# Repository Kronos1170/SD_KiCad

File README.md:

# IBM Card Reader

KiCad 10 project for the IBM card reader prototype board (ESP32-S3).

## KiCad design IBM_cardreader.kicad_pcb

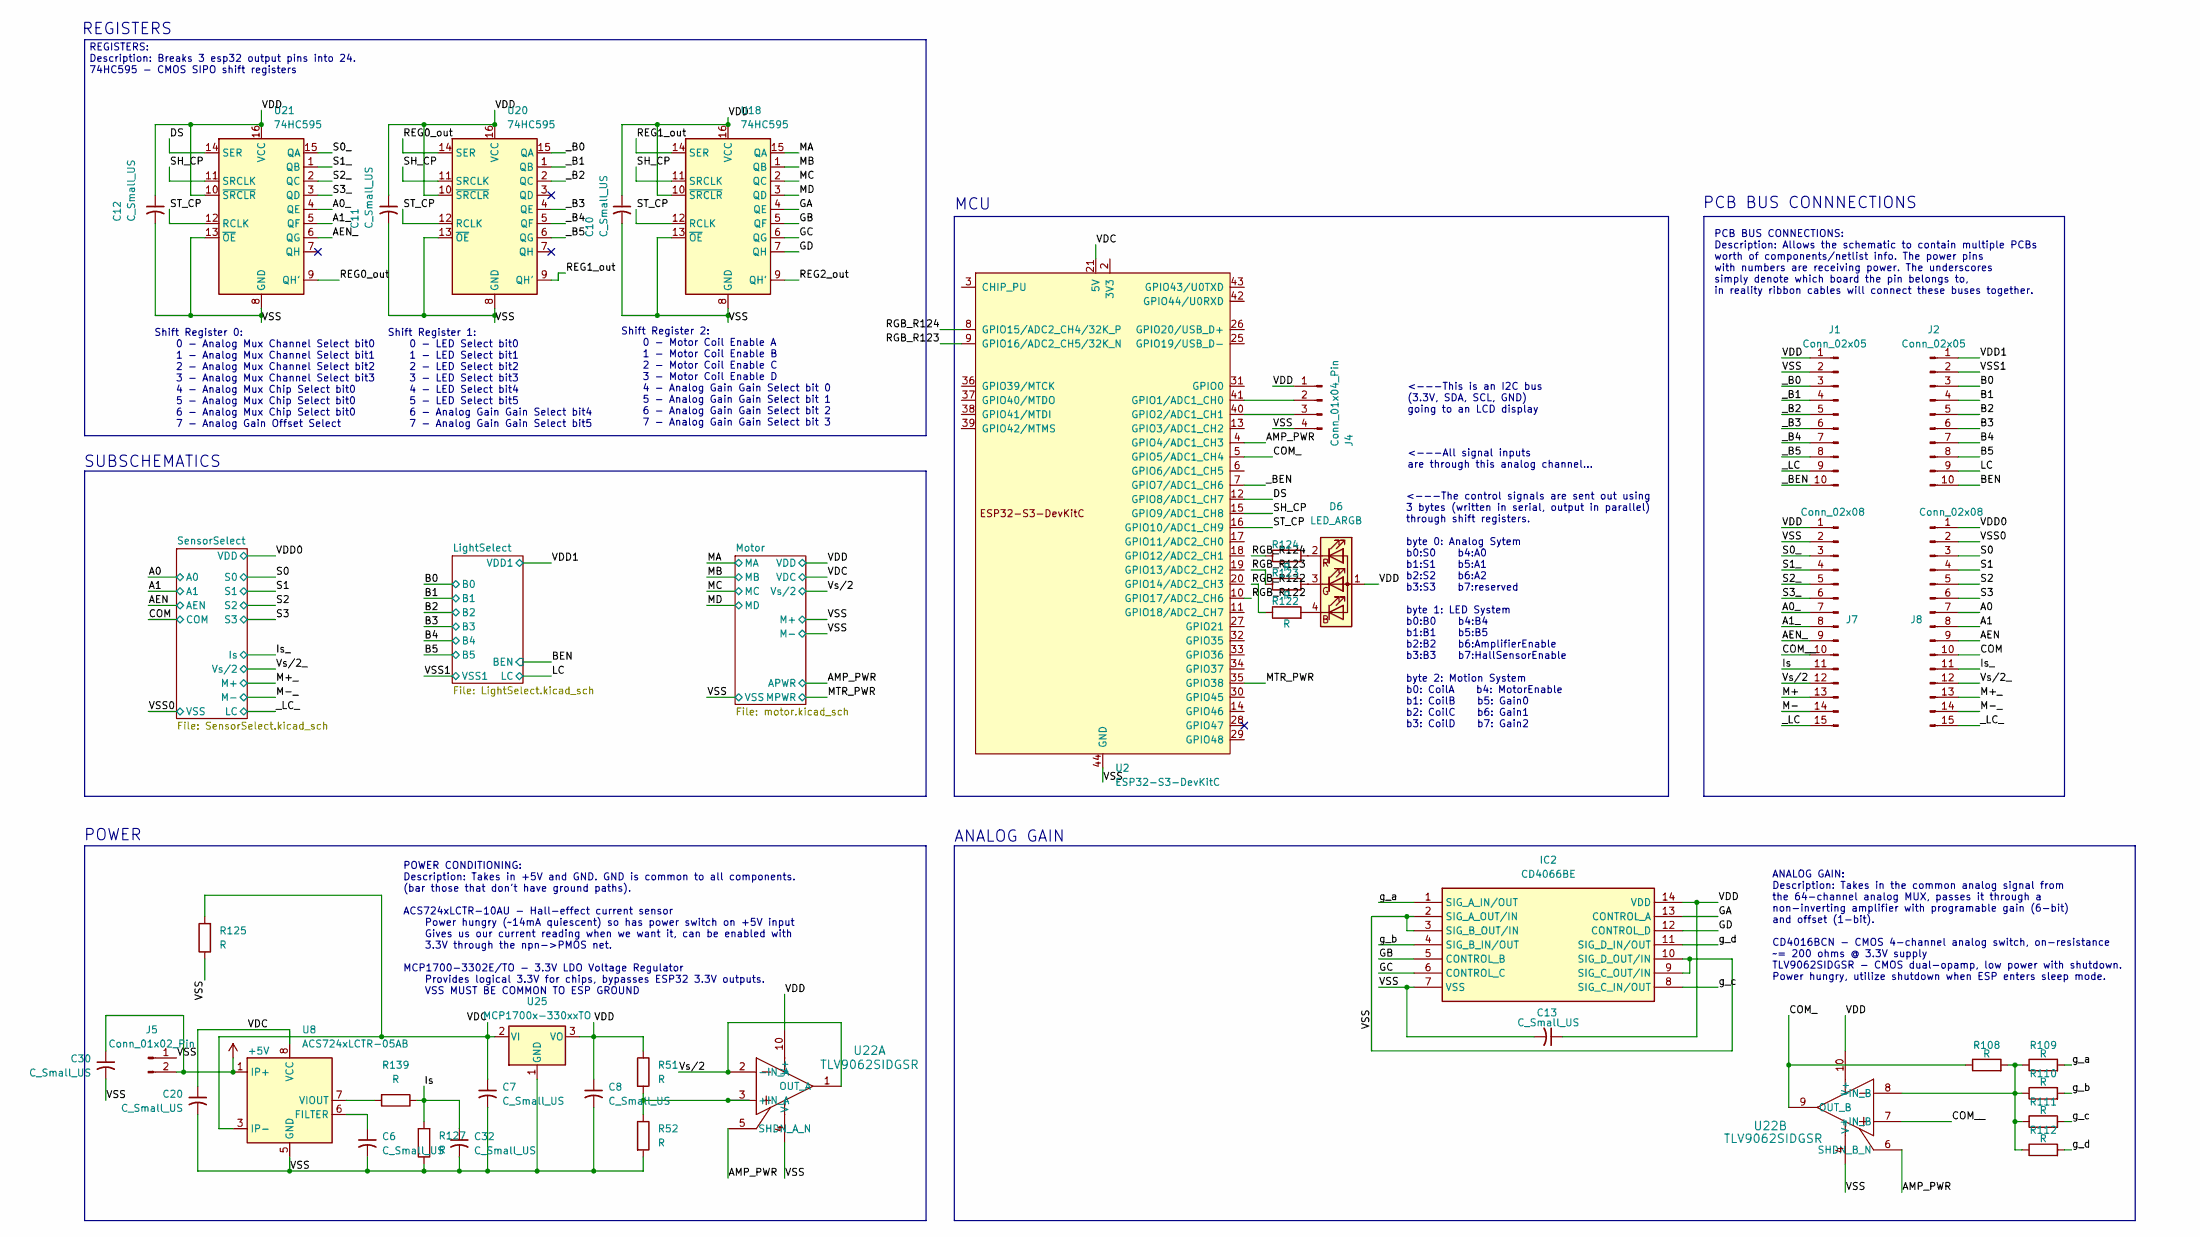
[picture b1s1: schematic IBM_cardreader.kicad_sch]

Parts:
C6, C7, C8, C10, C11, C12, C13, C20, C30, C32: C_Small_US; C_Disc_D3.0mm_W1.6mm_P2.50mm
D6: LED_ARGB; LED_RGB_1210
IC2: CD4066BE; DIP-14_W7.62mm; Mouser Part Number 595-CD4066BE
J1, J2: Conn_02x05; DIP-10_W7.62mm
J4: Conn_01x04_Pin; TerminalBlock_MaiXu_MX126-5.0-04P_1x04_P5.00mm
J5: Conn_01x02_Pin; TerminalBlock_MaiXu_MX126-5.0-02P_1x02_P5.00mm
J7, J8: Conn_02x08; DIP-16_W7.62mm
R51, R52, R108, R109, R110, R111, R112, R122, R123, R124, R125, R127, R139: R; R_Axial_DIN0207_L6.3mm_D2.5mm_P2.54mm_Vertical
U2: ESP32-S3-DevKitC
U8: ACS724xLCTR-05AB; DIP-8_W7.62mm
U18, U20, U21: 74HC595; DIP-16_W7.62mm
U22: TLV9062SIDGSR; TLV9062S_carrier
U25: MCP1700x-330xxTO; TO-92_Inline

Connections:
+5V: C30.1, J5.2, U8.1 (IP+), U8.2 (IP+)
/A0: J8.7; also elsewhere on the board
/A0_: J7.7, U21.4 (QE)
/A1: J8.8; also elsewhere on the board
/A1_: J7.8, U21.5 (QF)
/AEN: J8.9; also elsewhere on the board
/AEN_: J7.9, U21.6 (QG)
/AMP_PWR: U2.4 (GPIO4/ADC1_CH3), U22.5 (SHDN_A_N), U22.6 (SHDN_B_N); also elsewhere on the board
/B0: J2.3; also elsewhere on the board
/B1: J2.4; also elsewhere on the board
/B2: J2.5; also elsewhere on the board
/B3: J2.6; also elsewhere on the board
/B4: J2.7; also elsewhere on the board
/B5: J2.8; also elsewhere on the board
/BEN: J2.10; also elsewhere on the board
/COM: J8.10; also elsewhere on the board
/COM_: R108.1, U2.5 (GPIO5/ADC1_CH4), U22.9 (OUT_B)
/COM__: J7.10, U22.7 (+IN_B)
/DS: U2.12 (GPIO8/ADC1_CH7), U21.14 (SER)
/GA: IC2.13 (CONTROL_A), U18.4 (QE)
/GB: IC2.5 (CONTROL_B), U18.5 (QF)
/GC: IC2.6 (CONTROL_C), U18.6 (QG)
/GD: IC2.12 (CONTROL_D), U18.7 (QH)
/Is: C32.1, J7.11, R127.2, R139.1
/Is_: J8.11; also elsewhere on the board
/LC: J2.9; also elsewhere on the board
/M+: J7.13
/M+_: J8.13; also elsewhere on the board
/M-: J7.14
/M-_: J8.14; also elsewhere on the board
/MA: U18.15 (QA); also elsewhere on the board
/MB: U18.1 (QB); also elsewhere on the board
/MC: U18.2 (QC); also elsewhere on the board
/MD: U18.3 (QD); also elsewhere on the board
/MTR_PWR: U2.35 (GPIO38); also elsewhere on the board
/REG0_out: U20.14 (SER), U21.9 (QH')
/REG1_out: U18.14 (SER), U20.9 (QH')
/REG2_out: U18.9 (QH')
/RGB_R122: R122.1, U2.10 (GPIO17/ADC2_CH6)
/RGB_R123: R123.1, U2.9 (GPIO16/ADC2_CH5/32K_N)
/RGB_R124: R124.1, U2.8 (GPIO15/ADC2_CH4/32K_P)
/S0: J8.3; also elsewhere on the board
/S0_: J7.3, U21.15 (QA)
/S1: J8.4; also elsewhere on the board
/S1_: J7.4, U21.1 (QB)
/S2: J8.5; also elsewhere on the board
/S2_: J7.5, U21.2 (QC)
/S3: J8.6; also elsewhere on the board
/S3_: J7.6, U21.3 (QD)
/SH_CP: U2.15 (GPIO9/ADC1_CH8), U18.11 (SRCLK), U20.11 (SRCLK), U21.11 (SRCLK)
/ST_CP: U2.16 (GPIO10/ADC1_CH9), U18.12 (RCLK), U20.12 (RCLK), U21.12 (RCLK)
/VDC: C7.1, C20.1, R125.2, U2.21 (5V), U8.3 (IP-), U8.4 (IP-), U8.8 (VCC), U25.2 (VI); also elsewhere on the board
/VDD: C8.1, C10.1, C11.1, C12.1, C13.1, D6.1 (A), IC2.14 (VDD), J1.1, J4.1, J7.1, R51.1, U18.10 (~SRCLR), U18.16 (VCC), U20.10 (~SRCLR), U20.16 (VCC), U21.10 (~SRCLR), U21.16 (VCC), U22.10 (V+), U25.3 (VO); also elsewhere on the board
/VDD0: J8.1; also elsewhere on the board
/VDD1: J2.1; also elsewhere on the board
/VSS: C6.2, C7.2, C8.2, C10.2, C11.2, C12.2, C13.2, C20.2, C30.2, C32.2, IC2.2 (SIG_A_OUT/IN), IC2.3 (SIG_B_OUT/IN), IC2.7 (VSS), IC2.9 (SIG_C_OUT/IN), IC2.10 (SIG_D_OUT/IN), J1.2, J4.4, J5.1, J7.2, R52.2, R125.1, R127.1, U2.22 (GND), U2.23 (GND), U2.24 (GND), U2.44 (GND), U8.5 (GND), U18.8 (GND), U18.13 (~OE), U20.8 (GND), U20.13 (~OE), U21.8 (GND), U21.13 (~OE), U22.4 (V-), U25.1 (GND); also elsewhere on the board
/VSS0: J8.2; also elsewhere on the board
/VSS1: J2.2; also elsewhere on the board
/Vs/2: J7.12, U22.1 (OUT_A), U22.2 (-IN_A); also elsewhere on the board
/Vs/2_: J8.12; also elsewhere on the board
/_B0: J1.3, U20.15 (QA)
/_B1: J1.4, U20.1 (QB)
/_B2: J1.5, U20.2 (QC)
/_B3: J1.6, U20.4 (QE)
/_B4: J1.7, U20.5 (QF)
/_B5: J1.8, U20.6 (QG)
/_BEN: J1.10, U2.7 (GPIO7/ADC1_CH6)
/_LC: J1.9, J7.15
/_LC_: J8.15; also elsewhere on the board
/g_a: IC2.1 (SIG_A_IN/OUT), R109.2
/g_b: IC2.4 (SIG_B_IN/OUT), R110.2
/g_c: IC2.8 (SIG_C_IN/OUT), R111.2
/g_d: IC2.11 (SIG_D_IN/OUT), R112.2
unnamed: D6.4 (BK), R122.2
unnamed: D6.3 (GK), R123.2
unnamed: D6.2 (RK), R124.2
unnamed: J4.2, U2.41 (GPIO1/ADC1_CH0)
unnamed: J4.3, U2.40 (GPIO2/ADC1_CH1)
unnamed: U2.1 (3V3), U2.2 (3V3)
unnamed: C6.1, U8.6 (FILTER)
unnamed: R139.2, U8.7 (VIOUT)
unnamed: R51.2, R52.1, U22.3 (+IN_A)
unnamed: R108.2, R109.1, R110.1, R111.1, R112.1, U22.8 (-IN_B)

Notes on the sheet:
Shift Register 2: 0 - Motor Coil Enable A 1 - Motor Coil Enable B 2 - Motor Coil Enable C 3 - Motor Coil Enable D 4 - Analog Gain Gain Select bit 0 5 - Analog Gain Gain Select bit 1 6 - Analog Gain Gain Select bit 2 7 - Analog Gain Gain Select bit 3
SUBSCHEMATICS
REGISTERS
POWER
Shift Register 1: 0 - LED Select bit0 1 - LED Select bit1 2 - LED Select bit2 3 - LED Select bit3 4 - LED Select bit4 5 - LED Select bit5 6 - Analog Gain Gain Select bit4 7 - Analog Gain Gain Select bit5
<---This is an I2C bus (3.3V, SDA, SCL, GND) going to an LCD display
PCB BUS CONNECTIONS: Description: Allows the schematic to contain multiple PCBs worth of components/netlist info. The power pins with numbers are receiving power. The underscores simply denote which board the pin belongs to, in reality ribbon cables will connect these buses together.
<---The control signals are sent out using 3 bytes (written in serial, output in parallel) through shift registers. byte 0: Analog Sytem b0:S0 b4:A0 b1:S1 b5:A1 b2:S2 b6:A2 b3:S3 b7:reserved byte 1: LED System b0:B0 b4:B4 b1:B1 b5:B5 b2:B2 b6:AmplifierEnable b3:B3 b7:HallSensorEnable byte 2: Motion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
POWER CONDITIONING: Description: Takes in +5V and GND. GND is common to all components. (bar those that don't have ground paths). ACS724xLCTR-10AU - Hall-effect current sensor Power hungry (~14mA quiescent) so has power switch on +5V input Gives us our current reading when we want it, can be enable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
REGISTERS: Description: Breaks 3 esp32 output pins into 24. 74HC595 - CMOS SIPO shift registers
MCU
PCB BUS CONNNECTIONS
Shift Register 0: 0 - Analog Mux Channel Select bit0 1 - Analog Mux Channel Select bit1 2 - Analog Mux Channel Select bit2 3 - Analog Mux Channel Select bit3 4 - Analog Mux Chip Select bit0 5 - Analog Mux Chip Select bit0 6 - Analog Mux Chip Select bit0 7 - Analog Gain Offset Select
<---All signal inputs are through this analog channel...
ANALOG GAIN: Description: Takes in the common analog signal from the 64-channel analog MUX, passes it through a non-inverting amplifier with programable gain (6-bit) and offset (1-bit). CD4016BCN - CMOS 4-channel analog switch, on-resistance ~= 200 ohms @ 3.3V supply TLV9062SIDGSR - CMOS dual-opamp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
ANALOG GAIN

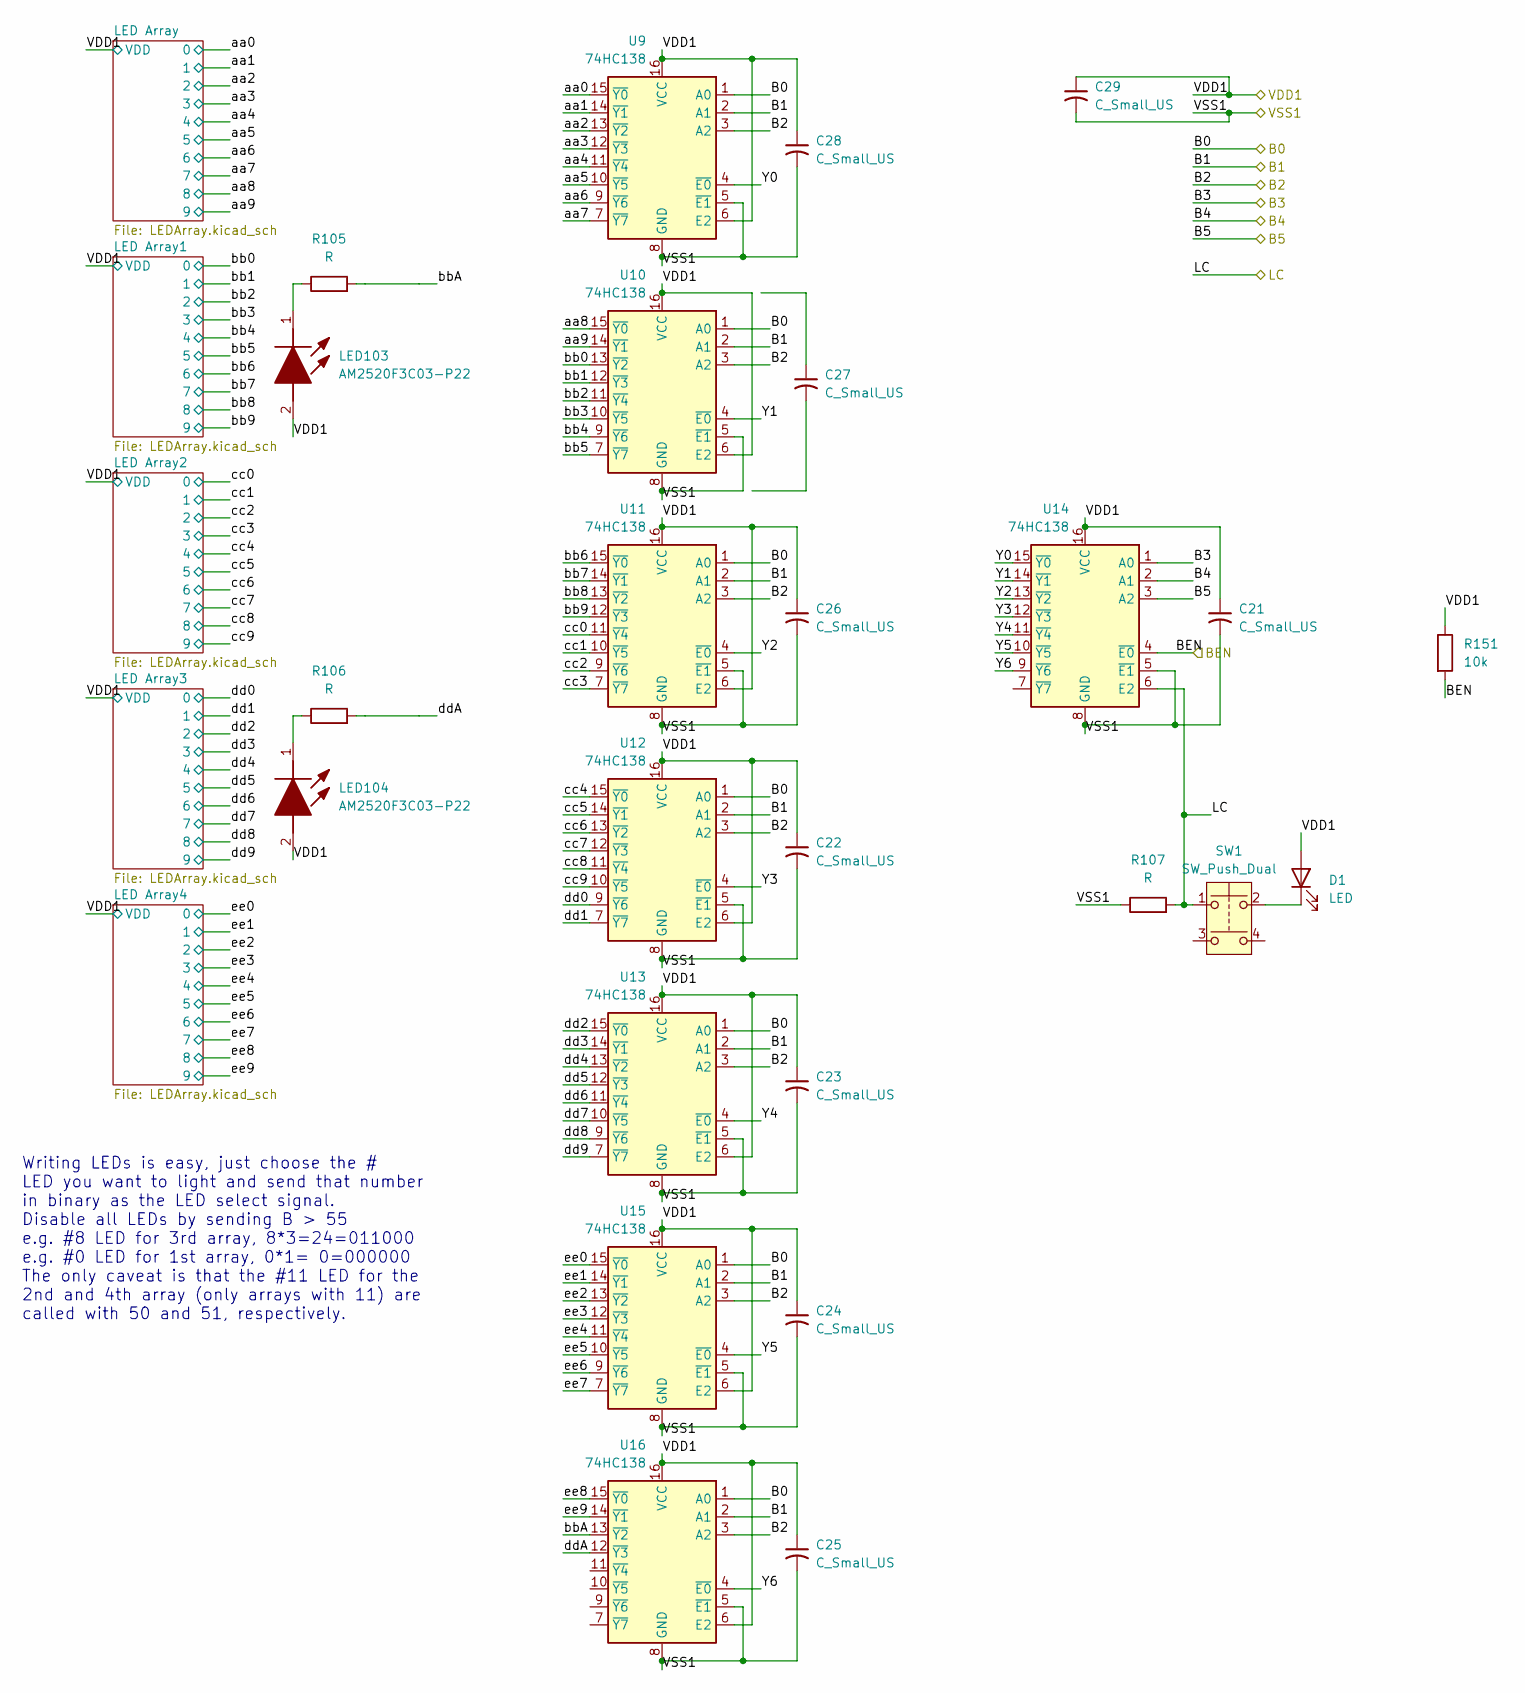
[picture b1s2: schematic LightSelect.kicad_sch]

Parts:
C21, C22, C23, C24, C25, C26, C27, C28, C29: C_Small_US; C_Disc_D3.0mm_W1.6mm_P2.50mm
D1: LED; LED_D5.0mm
LED103, LED104: AM2520F3C03-P22; Kingbright; Mouser Part Number 604-AM2520F3C03-P22
R105, R106, R107: R; R_Axial_DIN0207_L6.3mm_D2.5mm_P2.54mm_Vertical
R151: 10k; R_Axial_DIN0207_L6.3mm_D2.5mm_P2.54mm_Vertical
SW1: SW_Push_Dual; SW_PUSH_6mm_4pad
U9, U10, U11, U12, U13, U14, U15, U16: 74HC138; DIP-16_W7.62mm

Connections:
/B0: U9.1 (A0), U10.1 (A0), U11.1 (A0), U12.1 (A0), U13.1 (A0), U15.1 (A0), U16.1 (A0); also elsewhere on the board
/B1: U9.2 (A1), U10.2 (A1), U11.2 (A1), U12.2 (A1), U13.2 (A1), U15.2 (A1), U16.2 (A1); also elsewhere on the board
/B2: U9.3 (A2), U10.3 (A2), U11.3 (A2), U12.3 (A2), U13.3 (A2), U15.3 (A2), U16.3 (A2); also elsewhere on the board
/B3: U14.1 (A0); also elsewhere on the board
/B4: U14.2 (A1); also elsewhere on the board
/B5: U14.3 (A2); also elsewhere on the board
/BEN: R151.2, U14.4 (~E0); also elsewhere on the board
/LC: R107.2, SW1.1, U14.6 (E2); also elsewhere on the board
/LightSelect/Y0: U9.4 (~E0), U14.15 (~Y0)
/LightSelect/Y1: U10.4 (~E0), U14.14 (~Y1)
/LightSelect/Y2: U11.4 (~E0), U14.13 (~Y2)
/LightSelect/Y3: U12.4 (~E0), U14.12 (~Y3)
/LightSelect/Y4: U13.4 (~E0), U14.11 (~Y4)
/LightSelect/Y5: U14.10 (~Y5), U15.4 (~E0)
/LightSelect/Y6: U14.9 (~Y6), U16.4 (~E0)
/LightSelect/aa0: U9.15 (~Y0); also elsewhere on the board
/LightSelect/aa1: U9.14 (~Y1); also elsewhere on the board
/LightSelect/aa2: U9.13 (~Y2); also elsewhere on the board
/LightSelect/aa3: U9.12 (~Y3); also elsewhere on the board
/LightSelect/aa4: U9.11 (~Y4); also elsewhere on the board
/LightSelect/aa5: U9.10 (~Y5); also elsewhere on the board
/LightSelect/aa6: U9.9 (~Y6); also elsewhere on the board
/LightSelect/aa7: U9.7 (~Y7); also elsewhere on the board
/LightSelect/aa8: U10.15 (~Y0); also elsewhere on the board
/LightSelect/aa9: U10.14 (~Y1); also elsewhere on the board
/LightSelect/bb0: U10.13 (~Y2); also elsewhere on the board
/LightSelect/bb1: U10.12 (~Y3); also elsewhere on the board
/LightSelect/bb2: U10.11 (~Y4); also elsewhere on the board
/LightSelect/bb3: U10.10 (~Y5); also elsewhere on the board
/LightSelect/bb4: U10.9 (~Y6); also elsewhere on the board
/LightSelect/bb5: U10.7 (~Y7); also elsewhere on the board
/LightSelect/bb6: U11.15 (~Y0); also elsewhere on the board
/LightSelect/bb7: U11.14 (~Y1); also elsewhere on the board
/LightSelect/bb8: U11.13 (~Y2); also elsewhere on the board
/LightSelect/bb9: U11.12 (~Y3); also elsewhere on the board
/LightSelect/bbA: R105.2, U16.13 (~Y2)
/LightSelect/cc0: U11.11 (~Y4); also elsewhere on the board
/LightSelect/cc1: U11.10 (~Y5); also elsewhere on the board
/LightSelect/cc2: U11.9 (~Y6); also elsewhere on the board
/LightSelect/cc3: U11.7 (~Y7); also elsewhere on the board
/LightSelect/cc4: U12.15 (~Y0); also elsewhere on the board
/LightSelect/cc5: U12.14 (~Y1); also elsewhere on the board
/LightSelect/cc6: U12.13 (~Y2); also elsewhere on the board
/LightSelect/cc7: U12.12 (~Y3); also elsewhere on the board
/LightSelect/cc8: U12.11 (~Y4); also elsewhere on the board
/LightSelect/cc9: U12.10 (~Y5); also elsewhere on the board
/LightSelect/dd0: U12.9 (~Y6); also elsewhere on the board
/LightSelect/dd1: U12.7 (~Y7); also elsewhere on the board
/LightSelect/dd2: U13.15 (~Y0); also elsewhere on the board
/LightSelect/dd3: U13.14 (~Y1); also elsewhere on the board
/LightSelect/dd4: U13.13 (~Y2); also elsewhere on the board
/LightSelect/dd5: U13.12 (~Y3); also elsewhere on the board
/LightSelect/dd6: U13.11 (~Y4); also elsewhere on the board
/LightSelect/dd7: U13.10 (~Y5); also elsewhere on the board
/LightSelect/dd8: U13.9 (~Y6); also elsewhere on the board
/LightSelect/dd9: U13.7 (~Y7); also elsewhere on the board
/LightSelect/ddA: R106.2, U16.12 (~Y3)
/LightSelect/ee0: U15.15 (~Y0); also elsewhere on the board
/LightSelect/ee1: U15.14 (~Y1); also elsewhere on the board
/LightSelect/ee2: U15.13 (~Y2); also elsewhere on the board
/LightSelect/ee3: U15.12 (~Y3); also elsewhere on the board
/LightSelect/ee4: U15.11 (~Y4); also elsewhere on the board
/LightSelect/ee5: U15.10 (~Y5); also elsewhere on the board
/LightSelect/ee6: U15.9 (~Y6); also elsewhere on the board
/LightSelect/ee7: U15.7 (~Y7); also elsewhere on the board
/LightSelect/ee8: U16.15 (~Y0); also elsewhere on the board
/LightSelect/ee9: U16.14 (~Y1); also elsewhere on the board
/VDD1: C21.1, C22.1, C23.1, C24.1, C25.1, C26.1, C28.1, C29.1, D1.2 (A), LED103.2 (A), LED104.2 (A), R151.1, U9.6 (E2), U9.16 (VCC), U10.6 (E2), U10.16 (VCC), U11.6 (E2), U11.16 (VCC), U12.6 (E2), U12.16 (VCC), U13.6 (E2), U13.16 (VCC), U14.16 (VCC), U15.6 (E2), U15.16 (VCC), U16.6 (E2), U16.16 (VCC); also elsewhere on the board
/VSS1: C21.2, C22.2, C23.2, C24.2, C25.2, C26.2, C28.2, C29.2, R107.1, U9.5 (~E1), U9.8 (GND), U10.5 (~E1), U10.8 (GND), U11.5 (~E1), U11.8 (GND), U12.5 (~E1), U12.8 (GND), U13.5 (~E1), U13.8 (GND), U14.5 (~E1), U14.8 (GND), U15.5 (~E1), U15.8 (GND), U16.5 (~E1), U16.8 (GND); also elsewhere on the board
unnamed: D1.1 (K), SW1.2
unnamed: LED103.1 (K), R105.1
unnamed: LED104.1 (K), R106.1

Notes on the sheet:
Writing LEDs is easy, just choose the # LED you want to light and send that number in binary as the LED select signal. Disable all LEDs by sending B > 55 e.g. #8 LED for 3rd array, 8*3=24=011000 e.g. #0 LED for 1st array, 0*1= 0=000000 The only caveat is that the #11 LED for the 2nd and 4th array (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

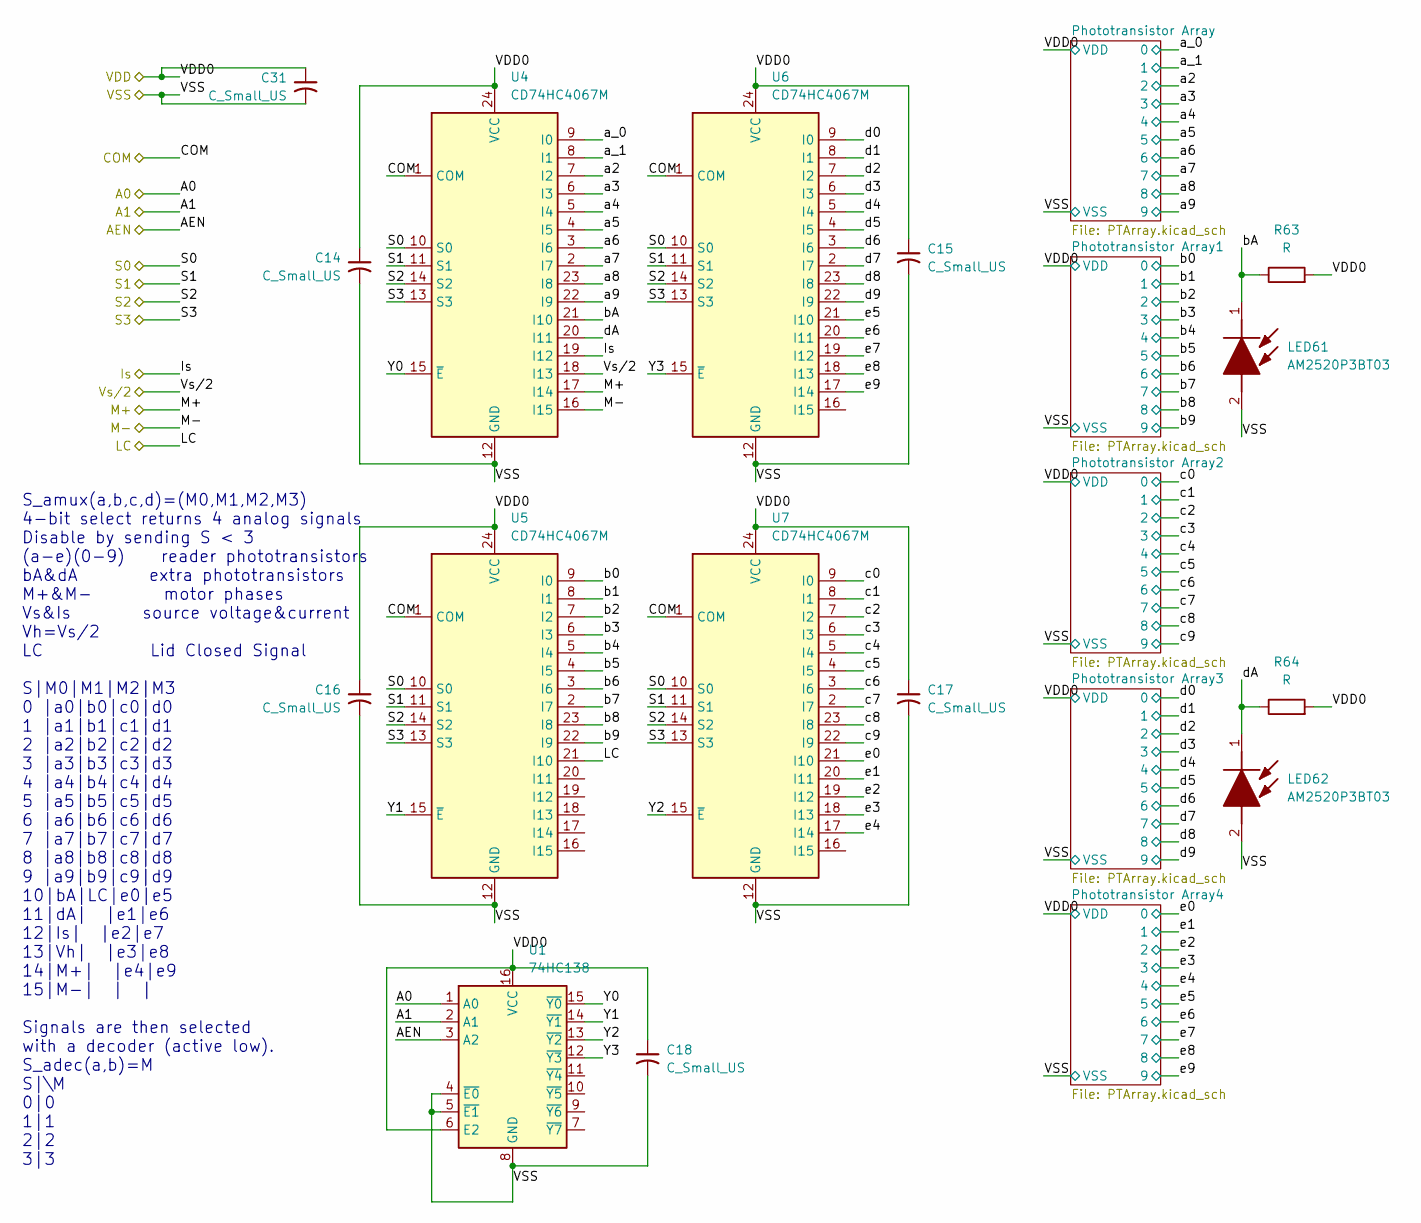
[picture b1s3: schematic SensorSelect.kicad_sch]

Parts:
C14, C15, C16, C17, C18, C31: C_Small_US; C_Disc_D3.0mm_W1.6mm_P2.50mm
LED61, LED62: AM2520P3BT03; Kingbright; Mouser Part Number 604-AM2520P3BT03
R63, R64: R; R_Axial_DIN0207_L6.3mm_D2.5mm_P2.54mm_Vertical
U1: 74HC138; DIP-16_W7.62mm
U4, U5, U6, U7: CD74HC4067M; CD74HC4067_carrier

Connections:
/A0: U1.1 (A0); also elsewhere on the board
/A1: U1.2 (A1); also elsewhere on the board
/AEN: U1.3 (A2); also elsewhere on the board
/COM: U4.1 (COM), U5.1 (COM), U6.1 (COM), U7.1 (COM); also elsewhere on the board
/Is_: U4.19 (I12); also elsewhere on the board
/M+_: U4.17 (I14); also elsewhere on the board
/M-_: U4.16 (I15); also elsewhere on the board
/S0: U4.10 (S0), U5.10 (S0), U6.10 (S0), U7.10 (S0); also elsewhere on the board
/S1: U4.11 (S1), U5.11 (S1), U6.11 (S1), U7.11 (S1); also elsewhere on the board
/S2: U4.14 (S2), U5.14 (S2), U6.14 (S2), U7.14 (S2); also elsewhere on the board
/S3: U4.13 (S3), U5.13 (S3), U6.13 (S3), U7.13 (S3); also elsewhere on the board
/SensorSelect/Y0: U1.15 (~Y0), U4.15 (~E)
/SensorSelect/Y1: U1.14 (~Y1), U5.15 (~E)
/SensorSelect/Y2: U1.13 (~Y2), U7.15 (~E)
/SensorSelect/Y3: U1.12 (~Y3), U6.15 (~E)
/SensorSelect/a2: U4.7 (I2); also elsewhere on the board
/SensorSelect/a3: U4.6 (I3); also elsewhere on the board
/SensorSelect/a4: U4.5 (I4); also elsewhere on the board
/SensorSelect/a5: U4.4 (I5); also elsewhere on the board
/SensorSelect/a6: U4.3 (I6); also elsewhere on the board
/SensorSelect/a7: U4.2 (I7); also elsewhere on the board
/SensorSelect/a8: U4.23 (I8); also elsewhere on the board
/SensorSelect/a9: U4.22 (I9); also elsewhere on the board
/SensorSelect/a_0: U4.9 (I0); also elsewhere on the board
/SensorSelect/a_1: U4.8 (I1); also elsewhere on the board
/SensorSelect/b0: U5.9 (I0); also elsewhere on the board
/SensorSelect/b1: U5.8 (I1); also elsewhere on the board
/SensorSelect/b2: U5.7 (I2); also elsewhere on the board
/SensorSelect/b3: U5.6 (I3); also elsewhere on the board
/SensorSelect/b4: U5.5 (I4); also elsewhere on the board
/SensorSelect/b5: U5.4 (I5); also elsewhere on the board
/SensorSelect/b6: U5.3 (I6); also elsewhere on the board
/SensorSelect/b7: U5.2 (I7); also elsewhere on the board
/SensorSelect/b8: U5.23 (I8); also elsewhere on the board
/SensorSelect/b9: U5.22 (I9); also elsewhere on the board
/SensorSelect/bA: LED61.1 (K), R63.1, U4.21 (I10)
/SensorSelect/c0: U7.9 (I0); also elsewhere on the board
/SensorSelect/c1: U7.8 (I1); also elsewhere on the board
/SensorSelect/c2: U7.7 (I2); also elsewhere on the board
/SensorSelect/c3: U7.6 (I3); also elsewhere on the board
/SensorSelect/c4: U7.5 (I4); also elsewhere on the board
/SensorSelect/c5: U7.4 (I5); also elsewhere on the board
/SensorSelect/c6: U7.3 (I6); also elsewhere on the board
/SensorSelect/c7: U7.2 (I7); also elsewhere on the board
/SensorSelect/c8: U7.23 (I8); also elsewhere on the board
/SensorSelect/c9: U7.22 (I9); also elsewhere on the board
/SensorSelect/d0: U6.9 (I0); also elsewhere on the board
/SensorSelect/d1: U6.8 (I1); also elsewhere on the board
/SensorSelect/d2: U6.7 (I2); also elsewhere on the board
/SensorSelect/d3: U6.6 (I3); also elsewhere on the board
/SensorSelect/d4: U6.5 (I4); also elsewhere on the board
/SensorSelect/d5: U6.4 (I5); also elsewhere on the board
/SensorSelect/d6: U6.3 (I6); also elsewhere on the board
/SensorSelect/d7: U6.2 (I7); also elsewhere on the board
/SensorSelect/d8: U6.23 (I8); also elsewhere on the board
/SensorSelect/d9: U6.22 (I9); also elsewhere on the board
/SensorSelect/dA: LED62.1 (K), R64.1, U4.20 (I11)
/SensorSelect/e0: U7.21 (I10); also elsewhere on the board
/SensorSelect/e1: U7.20 (I11); also elsewhere on the board
/SensorSelect/e2: U7.19 (I12); also elsewhere on the board
/SensorSelect/e3: U7.18 (I13); also elsewhere on the board
/SensorSelect/e4: U7.17 (I14); also elsewhere on the board
/SensorSelect/e5: U6.21 (I10); also elsewhere on the board
/SensorSelect/e6: U6.20 (I11); also elsewhere on the board
/SensorSelect/e7: U6.19 (I12); also elsewhere on the board
/SensorSelect/e8: U6.18 (I13); also elsewhere on the board
/SensorSelect/e9: U6.17 (I14); also elsewhere on the board
/VDD0: C14.1, C15.1, C16.1, C17.1, C18.1, C31.1, R63.2, R64.2, U1.6 (E2), U1.16 (VCC), U4.24 (VCC), U5.24 (VCC), U6.24 (VCC), U7.24 (VCC); also elsewhere on the board
/VSS0: C14.2, C15.2, C16.2, C17.2, C18.2, C31.2, LED61.2 (A), LED62.2 (A), U1.4 (~E0), U1.5 (~E1), U1.8 (GND), U4.12 (GND), U5.12 (GND), U6.12 (GND), U7.12 (GND); also elsewhere on the board
/Vs/2_: U4.18 (I13); also elsewhere on the board
/_LC_: U5.21 (I10); also elsewhere on the board

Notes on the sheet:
S_amux(a,b,c,d)=(M0,M1,M2,M3) 4-bit select returns 4 analog signals Disable by sending S < 3 (a-e)(0-9) reader phototransistors bA&dA extra phototransistors M+&M- motor phases Vs&Is source voltage&current Vh=Vs/2 LC Lid Closed Signal S|M0|M1|M2|M3 0 |a0|b0|c0|d0 1 |a1|b1|c1|d1 2 |a2|b2|c2|d2 3 |a3|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

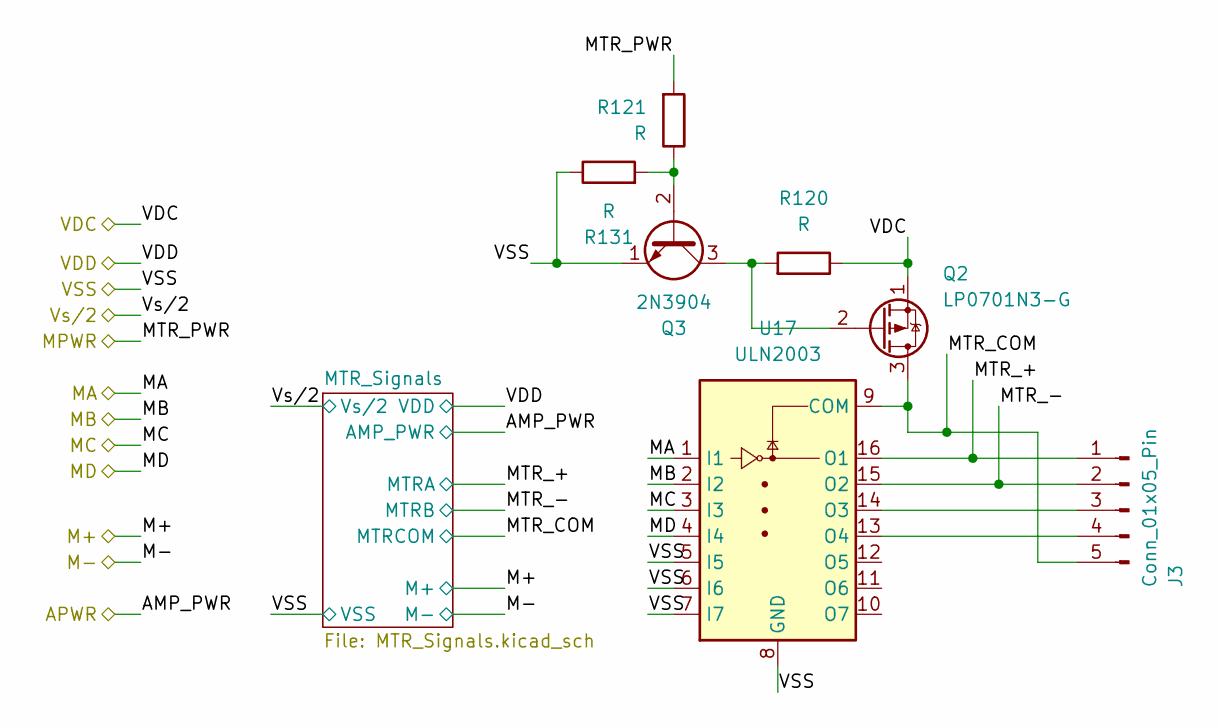
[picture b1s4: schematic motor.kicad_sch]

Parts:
J3: Conn_01x05_Pin; TerminalBlock_MaiXu_MX126-5.0-05P_1x05_P5.00mm
Q2: LP0701N3-G; TO-92_MC_MCH
Q3: 2N3904; TO-92_Inline
R120, R121, R131: R; R_Axial_DIN0207_L6.3mm_D2.5mm_P2.54mm_Vertical
U17: ULN2003; DIP-16_W7.62mm

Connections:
/MA: U17.1 (I1); also elsewhere on the board
/MB: U17.2 (I2); also elsewhere on the board
/MC: U17.3 (I3); also elsewhere on the board
/MD: U17.4 (I4); also elsewhere on the board
/MTR_PWR: R121.2; also elsewhere on the board
/Motor/MTR_+: J3.1, U17.16 (O1); also elsewhere on the board
/Motor/MTR_-: J3.2, U17.15 (O2); also elsewhere on the board
/Motor/MTR_COM: J3.5, Q2.3 (D), U17.9 (COM); also elsewhere on the board
/VDC: Q2.1 (S), R120.1; also elsewhere on the board
/VSS: Q3.1 (E), R131.1, U17.5 (I5), U17.6 (I6), U17.7 (I7), U17.8 (GND); also elsewhere on the board
unnamed: J3.3, U17.14 (O3)
unnamed: J3.4, U17.13 (O4)
unnamed: Q2.2 (G), Q3.3 (C), R120.2
unnamed: Q3.2 (B), R121.1, R131.2

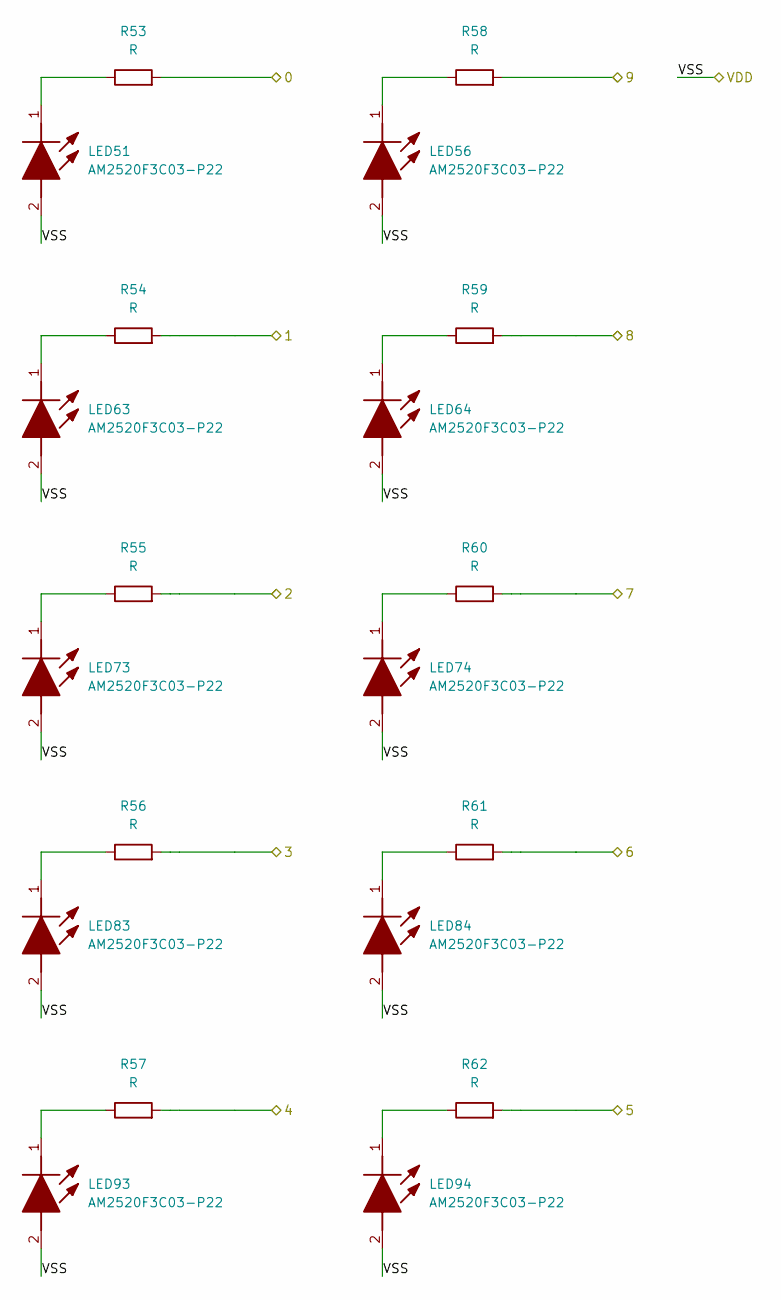
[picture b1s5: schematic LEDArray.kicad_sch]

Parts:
LED51, LED56, LED63, LED64, LED73, LED74, LED83, LED84, LED93, LED94: AM2520F3C03-P22; Kingbright; Mouser Part Number 604-AM2520F3C03-P22
R53, R54, R55, R56, R57, R58, R59, R60, R61, R62: R; R_Axial_DIN0207_L6.3mm_D2.5mm_P2.54mm_Vertical

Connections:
/LightSelect/aa0: R53.2; also elsewhere on the board
/LightSelect/aa1: R54.2; also elsewhere on the board
/LightSelect/aa2: R55.2; also elsewhere on the board
/LightSelect/aa3: R56.2; also elsewhere on the board
/LightSelect/aa4: R57.2; also elsewhere on the board
/LightSelect/aa5: R62.2; also elsewhere on the board
/LightSelect/aa6: R61.2; also elsewhere on the board
/LightSelect/aa7: R60.2; also elsewhere on the board
/LightSelect/aa8: R59.2; also elsewhere on the board
/LightSelect/aa9: R58.2; also elsewhere on the board
/VDD1: LED51.2 (A), LED56.2 (A), LED63.2 (A), LED64.2 (A), LED73.2 (A), LED74.2 (A), LED83.2 (A), LED84.2 (A), LED93.2 (A), LED94.2 (A); also elsewhere on the board
unnamed: LED51.1 (K), R53.1
unnamed: LED56.1 (K), R58.1
unnamed: LED63.1 (K), R54.1
unnamed: LED64.1 (K), R59.1
unnamed: LED73.1 (K), R55.1
unnamed: LED74.1 (K), R60.1
unnamed: LED83.1 (K), R56.1
unnamed: LED84.1 (K), R61.1
unnamed: LED93.1 (K), R57.1
unnamed: LED94.1 (K), R62.1

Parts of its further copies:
LED52, LED53, LED54, LED55, LED57, LED58, LED59, LED60, LED65, LED66, LED67, LED68, LED69, LED70, LED71, LED72, LED75, LED76, LED77, LED78, LED79, LED80, LED81, LED82, LED85, LED86, LED87, LED88, LED89, LED90, LED91, LED92, LED95, LED96, LED97, LED98, LED99, LED100, LED101, LED102: AM2520F3C03-P22; Kingbright; Mouser Part Number 604-AM2520F3C03-P22
R65, R66, R67, R68, R69, R70, R71, R72, R73, R74, R75, R76, R77, R78, R79, R80, R81, R82, R83, R84, R85, R86, R87, R88, R89, R90, R91, R92, R93, R94, R95, R96, R97, R98, R99, R100, R101, R102, R103, R104: R; R_Axial_DIN0207_L6.3mm_D2.5mm_P2.54mm_Vertical

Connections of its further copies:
/LightSelect/bb0: R65.2; also elsewhere on the board
/LightSelect/bb1: R66.2; also elsewhere on the board
/LightSelect/bb2: R67.2; also elsewhere on the board
/LightSelect/bb3: R68.2; also elsewhere on the board
/LightSelect/bb4: R69.2; also elsewhere on the board
/LightSelect/bb5: R74.2; also elsewhere on the board
/LightSelect/bb6: R73.2; also elsewhere on the board
/LightSelect/bb7: R72.2; also elsewhere on the board
/LightSelect/bb8: R71.2; also elsewhere on the board
/LightSelect/bb9: R70.2; also elsewhere on the board
/LightSelect/cc0: R75.2; also elsewhere on the board
/LightSelect/cc1: R76.2; also elsewhere on the board
/LightSelect/cc2: R77.2; also elsewhere on the board
/LightSelect/cc3: R78.2; also elsewhere on the board
/LightSelect/cc4: R79.2; also elsewhere on the board
/LightSelect/cc5: R84.2; also elsewhere on the board
/LightSelect/cc6: R83.2; also elsewhere on the board
/LightSelect/cc7: R82.2; also elsewhere on the board
/LightSelect/cc8: R81.2; also elsewhere on the board
/LightSelect/cc9: R80.2; also elsewhere on the board
/LightSelect/dd0: R85.2; also elsewhere on the board
/LightSelect/dd1: R86.2; also elsewhere on the board
/LightSelect/dd2: R87.2; also elsewhere on the board
/LightSelect/dd3: R88.2; also elsewhere on the board
/LightSelect/dd4: R89.2; also elsewhere on the board
/LightSelect/dd5: R94.2; also elsewhere on the board
/LightSelect/dd6: R93.2; also elsewhere on the board
/LightSelect/dd7: R92.2; also elsewhere on the board
/LightSelect/dd8: R91.2; also elsewhere on the board
/LightSelect/dd9: R90.2; also elsewhere on the board
/LightSelect/ee0: R95.2; also elsewhere on the board
/LightSelect/ee1: R96.2; also elsewhere on the board
/LightSelect/ee2: R97.2; also elsewhere on the board
/LightSelect/ee3: R98.2; also elsewhere on the board
/LightSelect/ee4: R99.2; also elsewhere on the board
/LightSelect/ee5: R104.2; also elsewhere on the board
/LightSelect/ee6: R103.2; also elsewhere on the board
/LightSelect/ee7: R102.2; also elsewhere on the board
/LightSelect/ee8: R101.2; also elsewhere on the board
/LightSelect/ee9: R100.2; also elsewhere on the board
/VDD1: LED52.2 (A), LED53.2 (A), LED54.2 (A), LED55.2 (A), LED57.2 (A), LED58.2 (A), LED59.2 (A), LED60.2 (A), LED65.2 (A), LED66.2 (A), LED67.2 (A), LED68.2 (A), LED69.2 (A), LED70.2 (A), LED71.2 (A), LED72.2 (A), LED75.2 (A), LED76.2 (A), LED77.2 (A), LED78.2 (A), LED79.2 (A), LED80.2 (A), LED81.2 (A), LED82.2 (A), LED85.2 (A), LED86.2 (A), LED87.2 (A), LED88.2 (A), LED89.2 (A), LED90.2 (A), LED91.2 (A), LED92.2 (A), LED95.2 (A), LED96.2 (A), LED97.2 (A), LED98.2 (A), LED99.2 (A), LED100.2 (A), LED101.2 (A), LED102.2 (A); also elsewhere on the board
unnamed: LED52.1 (K), R65.1
unnamed: LED53.1 (K), R75.1
unnamed: LED54.1 (K), R85.1
unnamed: LED55.1 (K), R95.1
unnamed: LED57.1 (K), R70.1
unnamed: LED58.1 (K), R80.1
unnamed: LED59.1 (K), R90.1
unnamed: LED60.1 (K), R100.1
unnamed: LED65.1 (K), R66.1
unnamed: LED66.1 (K), R71.1
unnamed: LED67.1 (K), R76.1
unnamed: LED68.1 (K), R81.1
unnamed: LED69.1 (K), R86.1
unnamed: LED70.1 (K), R91.1
unnamed: LED71.1 (K), R96.1
unnamed: LED72.1 (K), R101.1
unnamed: LED75.1 (K), R67.1
unnamed: LED76.1 (K), R72.1
unnamed: LED77.1 (K), R77.1
unnamed: LED78.1 (K), R82.1
unnamed: LED79.1 (K), R87.1
unnamed: LED80.1 (K), R92.1
unnamed: LED81.1 (K), R97.1
unnamed: LED82.1 (K), R102.1
unnamed: LED85.1 (K), R68.1
unnamed: LED86.1 (K), R73.1
unnamed: LED87.1 (K), R78.1
unnamed: LED88.1 (K), R83.1
unnamed: LED89.1 (K), R88.1
unnamed: LED90.1 (K), R93.1
unnamed: LED91.1 (K), R98.1
unnamed: LED92.1 (K), R103.1
unnamed: LED95.1 (K), R69.1
unnamed: LED96.1 (K), R74.1
unnamed: LED97.1 (K), R79.1
unnamed: LED98.1 (K), R84.1
unnamed: LED99.1 (K), R89.1
unnamed: LED100.1 (K), R94.1
unnamed: LED101.1 (K), R99.1
unnamed: LED102.1 (K), R104.1
